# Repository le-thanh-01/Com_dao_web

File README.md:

# 4S - Cơm đảo Bách Khoa

## Phần mềm đặt cơm đảo trực tuyến, xây dựng bằng **React + Vite**.

## Mục lục

- [Yêu cầu hệ thống](#yêu-cầu-hệ-thống)
- [Cài đặt và chạy trang](#cài-đặt-và-chạy-trang)
- [Cấu trúc thư mục](#cấu-trúc-thư-mục)
- [Kiến trúc dữ liệu](#kiến-trúc-dữ-liệu)
- [Logic giỏ hàng & Quota](#logic-giỏ-hàng--quota)
- [Danh sách trang](#danh-sách-trang)
- [CSS & Theme](#css--theme)
- [API mock](#api-mock)
- [Hướng dẫn mở rộng](#hướng-dẫn-mở-rộng)

---

## Yêu cầu hệ thống

| Công cụ | Phiên bản tối thiểu |
| ------- | ------------------- |
| Node.js | 18.x                |
| npm     | 9.x                 |

---

## Cài đặt và chạy trang

```bash
# Clone dự án về máy
git clone https://github.com/le-thanh-01/Com_dao_web

cd Com_dao_web

# Cài đặt dependencies
npm install

# Chạy môi trường development
npm run dev

# Build production
npm run build

# Preview build
npm run preview

# Push code mới lên gh-page
npm run deploy
```

Ứng dụng chạy mặc định tại `http://localhost:5173`.

---

## Cấu trúc thư mục

```
Com_dao_web/
├── public/
    ├── ico/                          # Lưu trữ các icon của web
    ├── img/                          # Các ảnh sử dụng trong trang web
    └── pages/
        ├── ref.html                  # Nguồn tham khảo
        ├── help.html                 # CSKH
        └── about.html                # Thông tin đội ngũ
├── system/
        └── api.js                    # Mock API — toàn bộ dữ liệu & endpoint giả lập
├── index.html
├── package.json              # Cấu hình thư viện và lệnh
├── src/
    ├── App.jsx                       # Router đơn giản theo page state
    ├── App.css                       # Layout .app, .app__body, .app__main
    ├── main.jsx                      # Entry point — AppProvider > App
    ├── context/
        ├── DataContext.jsx           # Server data provider + tất cả public hook
        ├── CartContext.jsx           # Giỏ hàng local + quota logic + sync server
        └── AppContext.jsx            # Gom các Provider vào thành 1 và tạo cầu nối giữa chúng (Bridge)
    ├── constants/
        └── footerLinks.js            # Nội dung và link điều hướng của Footer Component
    ├── styles/
        ├── variables.css             # CSS custom properties (màu, font, radius, transition)
        └── global.css                # Reset, scrollbar, @keyframes fadeUp
    └── components/
        ├── Skeleton/
            ├── Skeleton.jsx          # ProductCardSkeleton, NoticeRowSkeleton, Spinner, ...
            └── Skeleton.css
        ├── Navbar/
            ├── Navbar.jsx
            └── Navbar.css
        ├── Sidebar/
            ├── Sidebar.jsx
            └── Sidebar.css
        ├── FilterBar/
            ├── FilterBar.jsx
            └── FilterBar.css
        ├── ProductCard/
            ├── ProductCard.jsx       # ProductCard + ProductGrid + QuotaBanner
            └── ProductCard.css
        ├── Footer/
            ├── Footer.jsx
            └── Footer.css
        ├── UserMenu/
            ├── UserMenu.jsx
            └── UserMenu.css
        ├── Login/
            ├── Login.jsx             # Form đăng nhập + ẩn/hiện mật khẩu
            └── Login.css
        ├── Register/
            ├── Register.jsx          # Form đăng ký + validation
            └── Register.css
        ├── Account/
            ├── Account.jsx           # 4 panel: Profile, Settings, Orders, History
            └── Account.css
        ├── Notice/
            ├── Notice.jsx            # Trang thông báo + modal chi tiết
            └── Notice.css
        └── Checkout/
            ├── Checkout.jsx          # Đặt hàng: giỏ hàng, đặt bàn, thanh toán, hoá đơn
            └── Checkout.css
└── README.md
```

---

## Kiến trúc dữ liệu

### Luồng dữ liệu tổng quan

```
api.js (DB object)
   │
   ▼
DataProvider (DataContext.jsx)
   │  useResource(fetcher) — mỗi resource có { data, loading, error, refetch }
   │
   ├── useProducts()      → products[]
   ├── useCategories()    → categories[]
   ├── useFooterLinks()   → footerLinks{}
   ├── useUserProfile()   → user, updateProfile()
   ├── useUserSettings()  → settings, saveSettings()
   ├── useNotices()       → notices[], markRead(), markAllRead()
   ├── useOrders()        → orders[], cancelOrder(), confirmDelivery()
   └── useUserCart()      → userCart{}, updateUserCart()
          │
          ▼
       CartBridge (main.jsx)
          │  truyền products + initialCart + onCartChange
          ▼
       CartProvider (CartContext.jsx)
          │  debounce 600ms → onCartChange(cart) → updateUserCart → api.js
          │
          └── useCart() → cart, quota, getStatus(), handleIncrement(),
                          handleDecrement(), handleBedDecrement(), ...
```

### DataContext — pattern `useResource`

```js
const useResource = (fetcher) => {
  const [state, setState] = useState({ data: null, loading: true, error: null });
  useEffect(() => { fetcher().then(({ data, error }) => setState(...)); }, []);
  return { ...state, refetch };
};
```

Mọi resource server đều tuân theo pattern này. Khi cần thay API thật, chỉ cần sửa hàm fetcher trong `api.js` — interface của hook không đổi.

---

## Logic giỏ hàng & Quota

### Quy tắc quota

| Suất cơm trong giỏ | Topping được phép | Đồ uống được phép |
| :----------------: | :---------------: | :---------------: |
|         0          |         0         |         0         |
|         1          |         2         |         1         |
|         2          |         4         |         2         |
|         n          |       n × 2       |       n × 1       |

> **Ngoại lệ:** Suất cơm thêm (có `id = 25`) không được tính vào maxTopping và maxDrink.
> Để thêm ngoại lệ khác, bổ sung id vào `QUOTA_EXCLUDED_BED_IDS` trong `CartContext.jsx`.

### `evaluateProductQuota` — pure function

```
Input:  productId, targetCart (snapshot), productsList
Output: { isBlocked, isTopping, isDrink, qty }
```

Được tái sử dụng ở hai nơi:

- `getStatus(id)` — đọc từ `cart` (state hiện tại) để render UI
- `handleIncrement` — đọc từ `prevCart` bên trong `setCart(prev => ...)` để đảm bảo đúng thứ tự batch update

### Debounce sync lên server

```
User bấm tăng/giảm nhanh liên tục
    → mỗi thay đổi reset timer 600ms
    → chỉ gọi updateUserCart(cart) sau 600ms yên tĩnh cuối cùng
```

> **Lưu ý:** quá trình sync và lấy thông tin cart chỉ được thực hiện sau khi đăng nhập

---

## Danh sách trang

### Component pages

| Route (page state) | Component      | Mô tả                                           |
| ------------------ | -------------- | ----------------------------------------------- |
| `"home"`           | `App.jsx`      | Trang chủ — danh mục + lưới sản phẩm            |
| `"login"`          | `Login.jsx`    | Đăng nhập — SĐT + mật khẩu (ẩn/hiện)            |
| `"register"`       | `Register.jsx` | Đăng ký — form 2 cột + validation               |
| `"account"`        | `Account.jsx`  | Tài khoản — profile, cài đặt, đơn hàng, lịch sử |
| `"notices"`        | `Notice.jsx`   | Thông báo — lọc theo loại + modal chi tiết      |
| `"checkout"`       | `Checkout.jsx` | Thanh toán — đặt bàn, thanh toán, hoá đơn VAT   |

Điều hướng qua prop `onNavigate(page)` — không dùng React Router.

### HTML pages

| Tên        | Nơi chứa đường dẫn | Mô tả                                   |
| ---------- | ------------------ | --------------------------------------- |
| index.html | Com_dao_web/       | main page                               |
| help.html  | Navbar.jsx         | Thông tin chăm sóc khách hàng           |
| about.html | footerLinks.js     | Thông tin về quán/đội ngũ nhân viên/dev |
| ref.html   | footerLinks.js     | Tài liệu tham khảo                      |

> **Lưu ý:** có 1 số link điều hướng được đưa vào trong footerLinks.js

---

## CSS & Theme

Toàn bộ token màu sắc nằm trong `src/styles/variables.css`:

```css
:root {
  --bg: #111110; /* Nền toàn trang */
  --surface: #1a1a18; /* Card, navbar, sidebar */
  --surface2: #222220; /* Input, hover row */
  --surface3: #252523; /* Filter button */
  --border: #2e2e2c; /* Viền card, input */
  --text: #e8e6e1; /* Chữ chính */
  --text-muted: #7a7872; /* Chữ phụ, label */
  --text-dim: #4a4a48; /* Chữ mờ, hint */
  --accent: #c8a96e; /* Màu nhấn vàng */
  --accent-soft: rgba(200, 169, 110, 0.1);
  --accent-hover: #d4b87a;
  --red: #d64f3c; /* Cảnh báo, xoá */
}
```

### Chuyển đổi Light Mode

```js
// Bật light mode
document.documentElement.classList.add("light");

// Tắt (về dark)
document.documentElement.classList.remove("light");
```

Được điều khiển bởi toggle **"Giao diện tối"** trong `Account > PanelSettings`, lưu qua `api.updateUserSettings({ darkMode })`.

---

## API mock

File `src/api.js` mô phỏng toàn bộ server với độ trễ ngẫu nhiên (200–1300ms).

| Hàm                          | Method | Endpoint giả lập             |
| ---------------------------- | ------ | ---------------------------- |
| `fetchProducts()`            | GET    | /products                    |
| `fetchCategories()`          | GET    | /categories                  |
| `fetchFooterLinks()`         | GET    | /footer-links                |
| `fetchUserProfile()`         | GET    | /user/profile                |
| `updateUserProfile(fields)`  | PUT    | /user/profile                |
| `fetchUserSettings()`        | GET    | /user/settings               |
| `updateUserSettings(patch)`  | PUT    | /user/settings               |
| `fetchUserCart()`            | GET    | /cart                        |
| `updateUserCart(cartData)`   | PUT    | /cart                        |
| `fetchOrders()`              | GET    | /orders                      |
| `placeOrder(payload)`        | POST   | /orders                      |
| `cancelOrder(id)`            | PATCH  | /orders/:id/cancel           |
| `confirmDelivery(id)`        | PATCH  | /orders/:id/confirm-delivery |
| `fetchNotices()`             | GET    | /notices                     |
| `markNoticeRead(id)`         | PATCH  | /notices/:id/read            |
| `markAllNoticesRead()`       | PATCH  | /notices/read-all            |
| `validatePromo(code)`        | POST   | /promo/validate              |
| `login({ phone, password })` | POST   | /auth/login                  |
| `register(fields)`           | POST   | /auth/register               |

Mọi hàm trả về `{ data, error }` — không bao giờ throw, caller luôn xử lý được.

---

## Hướng dẫn mở rộng

### Thay API thật vào

```js
// api.js — thay delay + DB bằng fetch thật
export async function fetchProducts() {
  const res = await fetch("/api/products", {
    headers: { Authorization: `Bearer ${token}` },
  });
  const data = await res.json();
  return { data, error: null };
}
```

Interface `{ data, error }` không thay đổi → DataContext và các hook không cần sửa.

### Thêm trang mới

```js
// App.jsx
if (page === "newpage") return <NewPage onNavigate={setPage} />;
```

```jsx
// Navbar.jsx — thêm vào NAV_LINKS và onClick handler
const NAV_LINKS = ["Trang chủ", "Thông báo", "CSKH", "NAV_LINK mới"];

<ul className="navbar__links">
  {NAV_LINKS.map((link) => (
    <li key={link}>
      <a
        href="#"
        className={
          (link === "Trang chủ" && currentPage === "home") ||
          (link === "Thông báo" && currentPage === "notices") ||
          link === "NAV_LINK mới"
            ? "active"
            : ""
        }
        onClick={(e) => {
          e.preventDefault();
          if (link === "Trang chủ") onNavigate?.("home");
          if (link === "Thông báo") onNavigate?.("notices");
          if (link === "NAV_LINK mới") onNavigate?.("newpage");
          if (link === "CSKH") {
            // Trả về '/' hoặc '/ten-repo/'
            const baseUrl = import.meta.env.BASE_URL;
            const path = `${baseUrl.endsWith("/") ? baseUrl : baseUrl + "/"}pages/help.html`;
            window.open(path, "_blank");
          }
          //hoặc dùng window.open mở tab mới
          if (link === "NAV_LINK mới") {
            // Trả về '/' hoặc '/ten-repo/'
            const baseUrl = import.meta.env.BASE_URL;
            const path = `${baseUrl.endsWith("/") ? baseUrl : baseUrl + "/"}pages/newpage.html`;
            window.open(path, "_blank");
          }
        }}
      >
        {link === "Thông báo" ? (
          <span className="notice-trigger">
            {link}
            {unreadCount > 0 && <span className="notice-trigger__dot" />}
          </span>
        ) : (
          link
        )}
      </a>
    </li>
  ))}
</ul>;
```

```js
//footerLinks.js
export const SOCIALS = [
  { icon: "𝕏", link: "https://x.com/?lang=vi" },
  { icon: "Z", link: "https://zalo.me/pc" },
  { icon: "f", link: "https://www.facebook.com/?locale=vi_VN" },
  { icon: "ig", link: "https://www.instagram.com/" },
  { icon: "i", link: path + "ref.html" },
  //{ icon: "nội dung icon mới (có thể là html String)", link: "đường dẫn mới" }
];

export const FOOTER_LINKS = {
  "Về chúng tôi": [
    { content: "Giới thiệu", link: path + "about.html" },
    { content: "Góp ý", link: "#" }, //thay # bằng đường dẫn thật
    { content: "Báo lỗi", link: "#" },
  ],
  "Khám phá": [
    { content: "Chính sách bảo mật", link: "#" },
    { content: "Điều khoản dịch vụ", link: "#" },
    {
      content: "Chính sách hợp tác",
      link: "https://le-thanh-01.github.io/game_of_life/",
    },
  ],
  /*
  "Mục mới": [
  {content: "Nội dung mới", link: "đường link mới"},
  ],
*/
};
```

**Lưu ý:** Trường hợp trang mới là html độp lập, file html nên được đưa vào public/pages/

Nếu file html cũng dùng react hoặc tái sử dụng các thành phần của index.html, thì nên để cùng cấp với index.html và khai báo trong vite.config.js:

```js
//vite.config.js
export default defineConfig({
  plugins: [react()],
  base: "/Com_dao_web/",
  build: {
    rollupOptions: {
      // Khai báo các điểm đầu vào (Entry points) của dự án
      input: {
        main: resolve(__dirname, "index.html"),
        about: resolve(__dirname, "about.html"),
        // Nếu có thêm trang, cứ khai báo tiếp ở đây (ví dụ: contact: resolve(...))
      },
    },
  },
});
```

### Thêm skeleton mới

```jsx
// Skeleton.jsx
export function MyFeatureSkeleton() {
  return (
    <div className="my-skeleton">
      <Skeleton height="14px" width="60%" />
      <Skeleton height="38px" radius="8px" />
    </div>
  );
}
```

### Thêm sản phẩm mới

#### Chỉnh sửa trực tiếp trong database hoặc DB mô phỏng tại api.js:

```js
//api.js
const DB = {
  products: [
    //set
    {
      id: 1,
      name: "Lạp xưởng + bò + đậu",
      price: "33.000đ",
      cats: ["best-seller", "set"],
      url: "/img/lap-xuong-bo-dau.jpg",
      badge: "hot",
    },
    ...{
      id: 102,
      name: "Coca",
      price: "10.000đ",
      cats: ["drink"],
      url: "/img/coca.jpg",
    },
    {
      id: 3004,
      name: "Chả giò",
      price: "10.000đ",
      cats: ["topping"],
      url: "/img/cha-gio.jpg",
    },
  ],
};
```

**Lưu ý:** mục cats của product phải tồn tại trong category, badge có thể thiết lập là **"hot"** hoặc **"new"**

#### Có thể thêm category mới:

```js
//api.js
  categories: [
    { id: "best-seller", label: "Best seller" },
    { id: "set", label: "Set" },
    { id: "bed", label: "Cơm" },
    { id: "topping", label: "Topping" },
    { id: "drink", label: "Đồ uống" },
    { id: "bootleg",label:"đè tem"}
  ],
```

Các trường khác có thể bổ sung theo cách tương tự

#### Thay đổi logic tính toán

Các ràng buộc về product được cấu hình trong context/CartContext.jsx:

```jsx
//CartContext.jsx

//Bổ sung suất cơm ngoại lệ (suất cơm sẽ không được sử dụng để mở thêm số topping và drink được phép)
const QUOTA_EXCLUDED_BED_IDS = new Set([25, 36]);

//Thay đổi ràng buộc giới hạn topping và drink trong evaluateProductQuota và quota
const evaluateProductQuota = (productId, targetCart, productsList) => {
  ...
  const maxToppings = totalBeds * 3;
  ...
  const maxDrinks = totalBeds * 2;
}
...
const quota = useMemo(() => {
...
const maxToppings = totalBeds * 3;
const maxDrinks = totalBeds * 2;
...
})
//Lưu ý: giá trị của maxToppings và maxDrinks trong cả 2 hàm phải giống nhau

//Xử lý khi xung đột giữa số lượng suất cơm và số toppings/drinks đã chọn
const clearExtrasAfterBedDecrement = (updatedCart, productsList) => {

  const countableBeds = getCountableBeds(productsList);
  const remainingBeds = countableBeds.reduce(
    (s, p) => s + (updatedCart[p.id] || 0),
    0,
  );

  if (remainingBeds > 0) return updatedCart;

  const result = { ...updatedCart };
  productsList.forEach((p) => {
    if (p.cats?.includes("topping") || p.cats?.includes("drink")) {
      delete result[p.id];
    }
  });
  return result;
};
```

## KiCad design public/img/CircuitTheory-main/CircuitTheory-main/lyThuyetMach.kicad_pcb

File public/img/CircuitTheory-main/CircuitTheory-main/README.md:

# CircuitTheory
Circuit Theory 2025.2 class

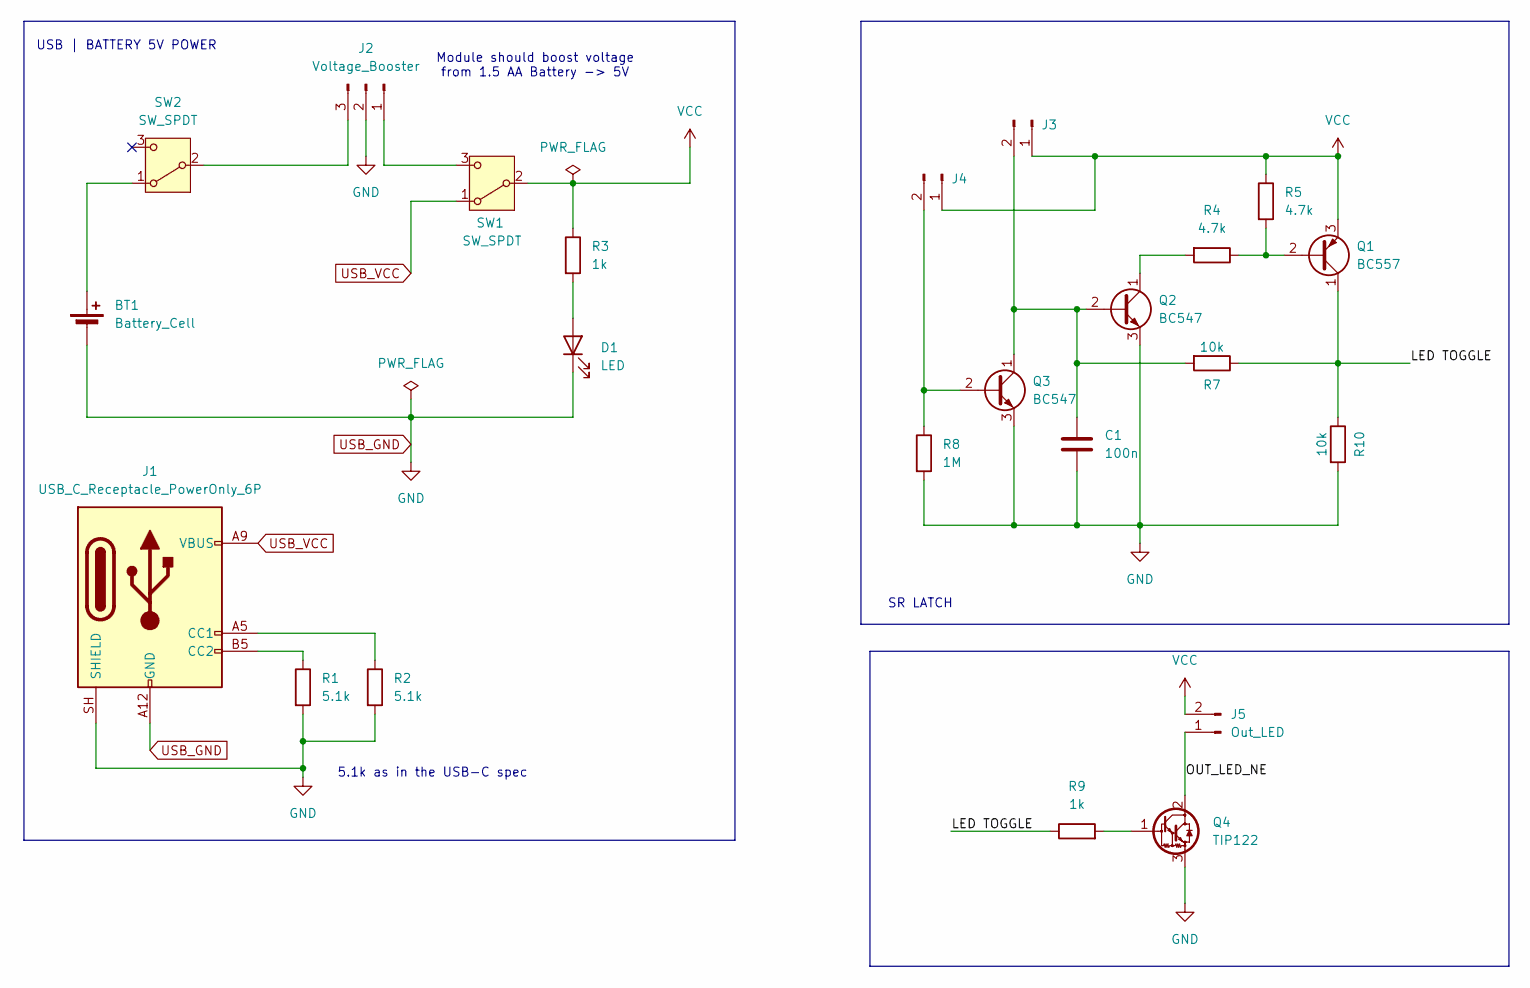
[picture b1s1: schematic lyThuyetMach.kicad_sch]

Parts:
BT1: Battery_Cell; BatteryHolder_Keystone_2460_1xAA
C1: 100n; C_Radial_D5.0mm_H5.0mm_P2.00mm
D1: LED; LED_D5.0mm_FlatTop
J1: USB_C_Receptacle_PowerOnly_6P; USB_C_Receptacle_HRO_TYPE-C-31-M-17
J2: Voltage_Booster; PinHeader_1x03_P2.54mm_Vertical
J3, J4: Conn_01x02_Pin; R_0815_2038Metric_Pad1.20x4.05mm_HandSolder
J5: Out_LED; PinHeader_1x02_P2.54mm_Vertical
Q1: BC557; TO-92_Inline
Q2, Q3: BC547; TO-92_Inline
Q4: TIP122; TO-220-3_Vertical
R1, R2: 5.1k; R_Axial_DIN0207_L6.3mm_D2.5mm_P10.16mm_Horizontal
R3, R9: 1k; R_Axial_DIN0207_L6.3mm_D2.5mm_P10.16mm_Horizontal
R4, R5: 4.7k; R_Axial_DIN0207_L6.3mm_D2.5mm_P10.16mm_Horizontal
R7, R10: 10k; R_Axial_DIN0207_L6.3mm_D2.5mm_P10.16mm_Horizontal
R8: 1M; R_Axial_DIN0207_L6.3mm_D2.5mm_P10.16mm_Horizontal
SW1, SW2: SW_SPDT; PinHeader_1x03_P2.54mm_Vertical

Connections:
/LED TOGGLE: Q1.1 (C), R7.1, R9.1, R10.1
/OUT_LED_NE: J5.1, Q4.2 (C)
unnamed: BT1.1 (+), SW2.1 (A)
unnamed: D1.2 (A), R3.2
unnamed: J1.A5 (CC1), R2.1
unnamed: J1.B5 (CC2), R1.1
unnamed: J2.1, SW1.3 (C)
unnamed: J2.3, SW2.2 (B)
unnamed: C1.1, J3.2, Q2.2 (B), Q3.1 (C), R7.2
unnamed: J4.2, Q3.2 (B), R8.1
unnamed: Q1.2 (B), R4.1, R5.2
unnamed: Q2.1 (C), R4.2
unnamed: Q4.1 (B), R9.2
USB_GND: BT1.2 (-), C1.2, D1.1 (K), J1.A12 (GND), J1.B12 (GND), J1.SH (SHIELD), J2.2, Q2.3 (E), Q3.3 (E), Q4.3 (E), R1.2, R2.2, R8.2, R10.2
USB_VCC: J1.A9 (VBUS), J1.B9 (VBUS), SW1.1 (A)
VCC: J3.1, J4.1, J5.2, Q1.3 (E), R3.1, R5.1, SW1.2 (B)

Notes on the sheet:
SR LATCH
USB | BATTERY 5V POWER
5.1k as in the USB-C spec
Module should boost voltage from 1.5 AA Battery -> 5V

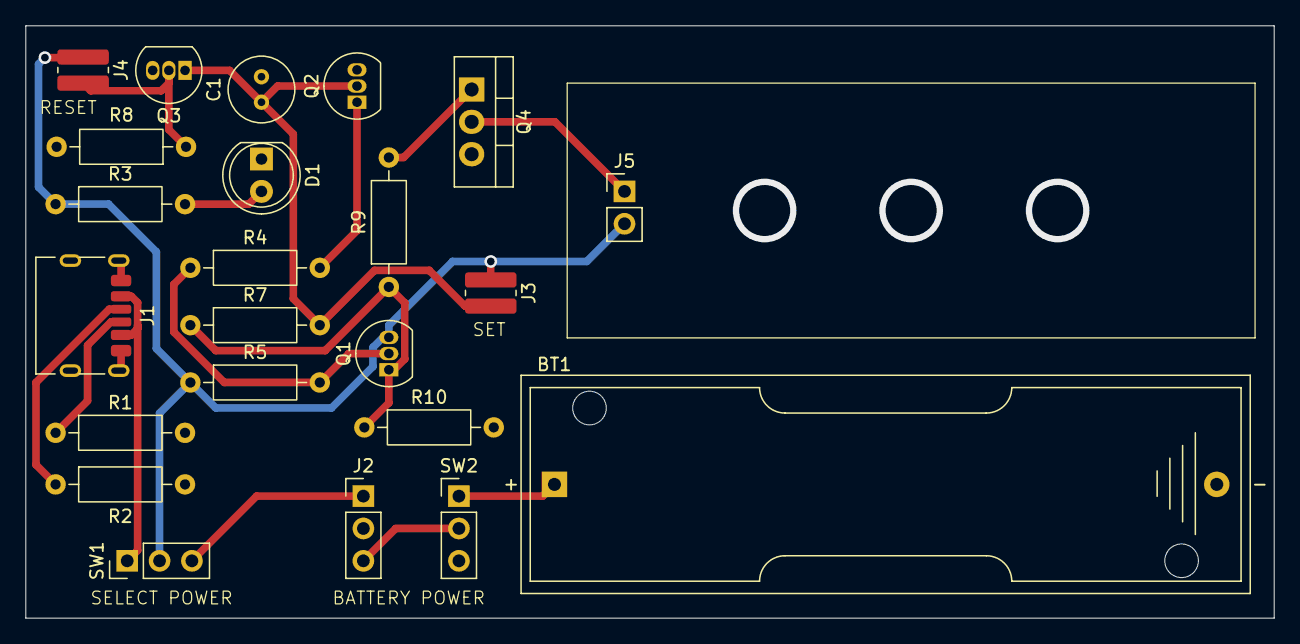
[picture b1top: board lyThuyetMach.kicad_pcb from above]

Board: 2 copper layers, 98.0 x 46.5 mm, 23 parts (0 on the bottom side), 16 nets.

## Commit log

2026-04-13 fix the images URL
2026-04-13 fix the URLs
2026-04-25 Add initial README first time
    This README provides an overview of the 4S online rice ordering software, including system requirements, installation instructions, directory structure, data architecture, cart logic, page listings, 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
2026-04-25 fix bugs and add some features
2026-04-26 add new set and move html sub-pages to public/pages
2026-04-26 fix conflict in vite.config
2026-05-28 update api.js to send data to server
2026-06-22 version 2.0.0: replace simulateDB by SpringBoot DB, and add some features
2026-06-23 v2.0.1: fix some bugs
2026-06-23 v2.0.2: flexible server url
2026-06-23 version 2.0.3: fix register and cart errors
2026-06-23 ver 2.0.4: fetchNotice now dont require loginState
2026-06-24 v2.0.5
2026-06-24 version 2.0.5: fix invoice and cart errors
2026-06-26 fix delUser
2026-06-26 version 2.0.5
